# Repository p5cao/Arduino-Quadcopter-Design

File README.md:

# Arduino-Quadcopter-Design
A creative class project to design the PCB board for a quadcopter as well as programming the firmware and implementing the PID controller for flight controls.
The picture of our quadcopter can be found on this gallery webpage.
https://photos.google.com/share/AF1QipN9F1jDYG9cubRXA-CwWNmIePdVq3RI0pVtxd35Kb-5K7d3aRKYkmTJEXwJQgeCqA/photo/AF1QipMYG6V8wfTyHqf-2jjKtqaBbs2ouibxToXAU-El?key=cHRpcUZwaGp2eWJNbW5EVUltc3VJQ0NNVlZvN3FB

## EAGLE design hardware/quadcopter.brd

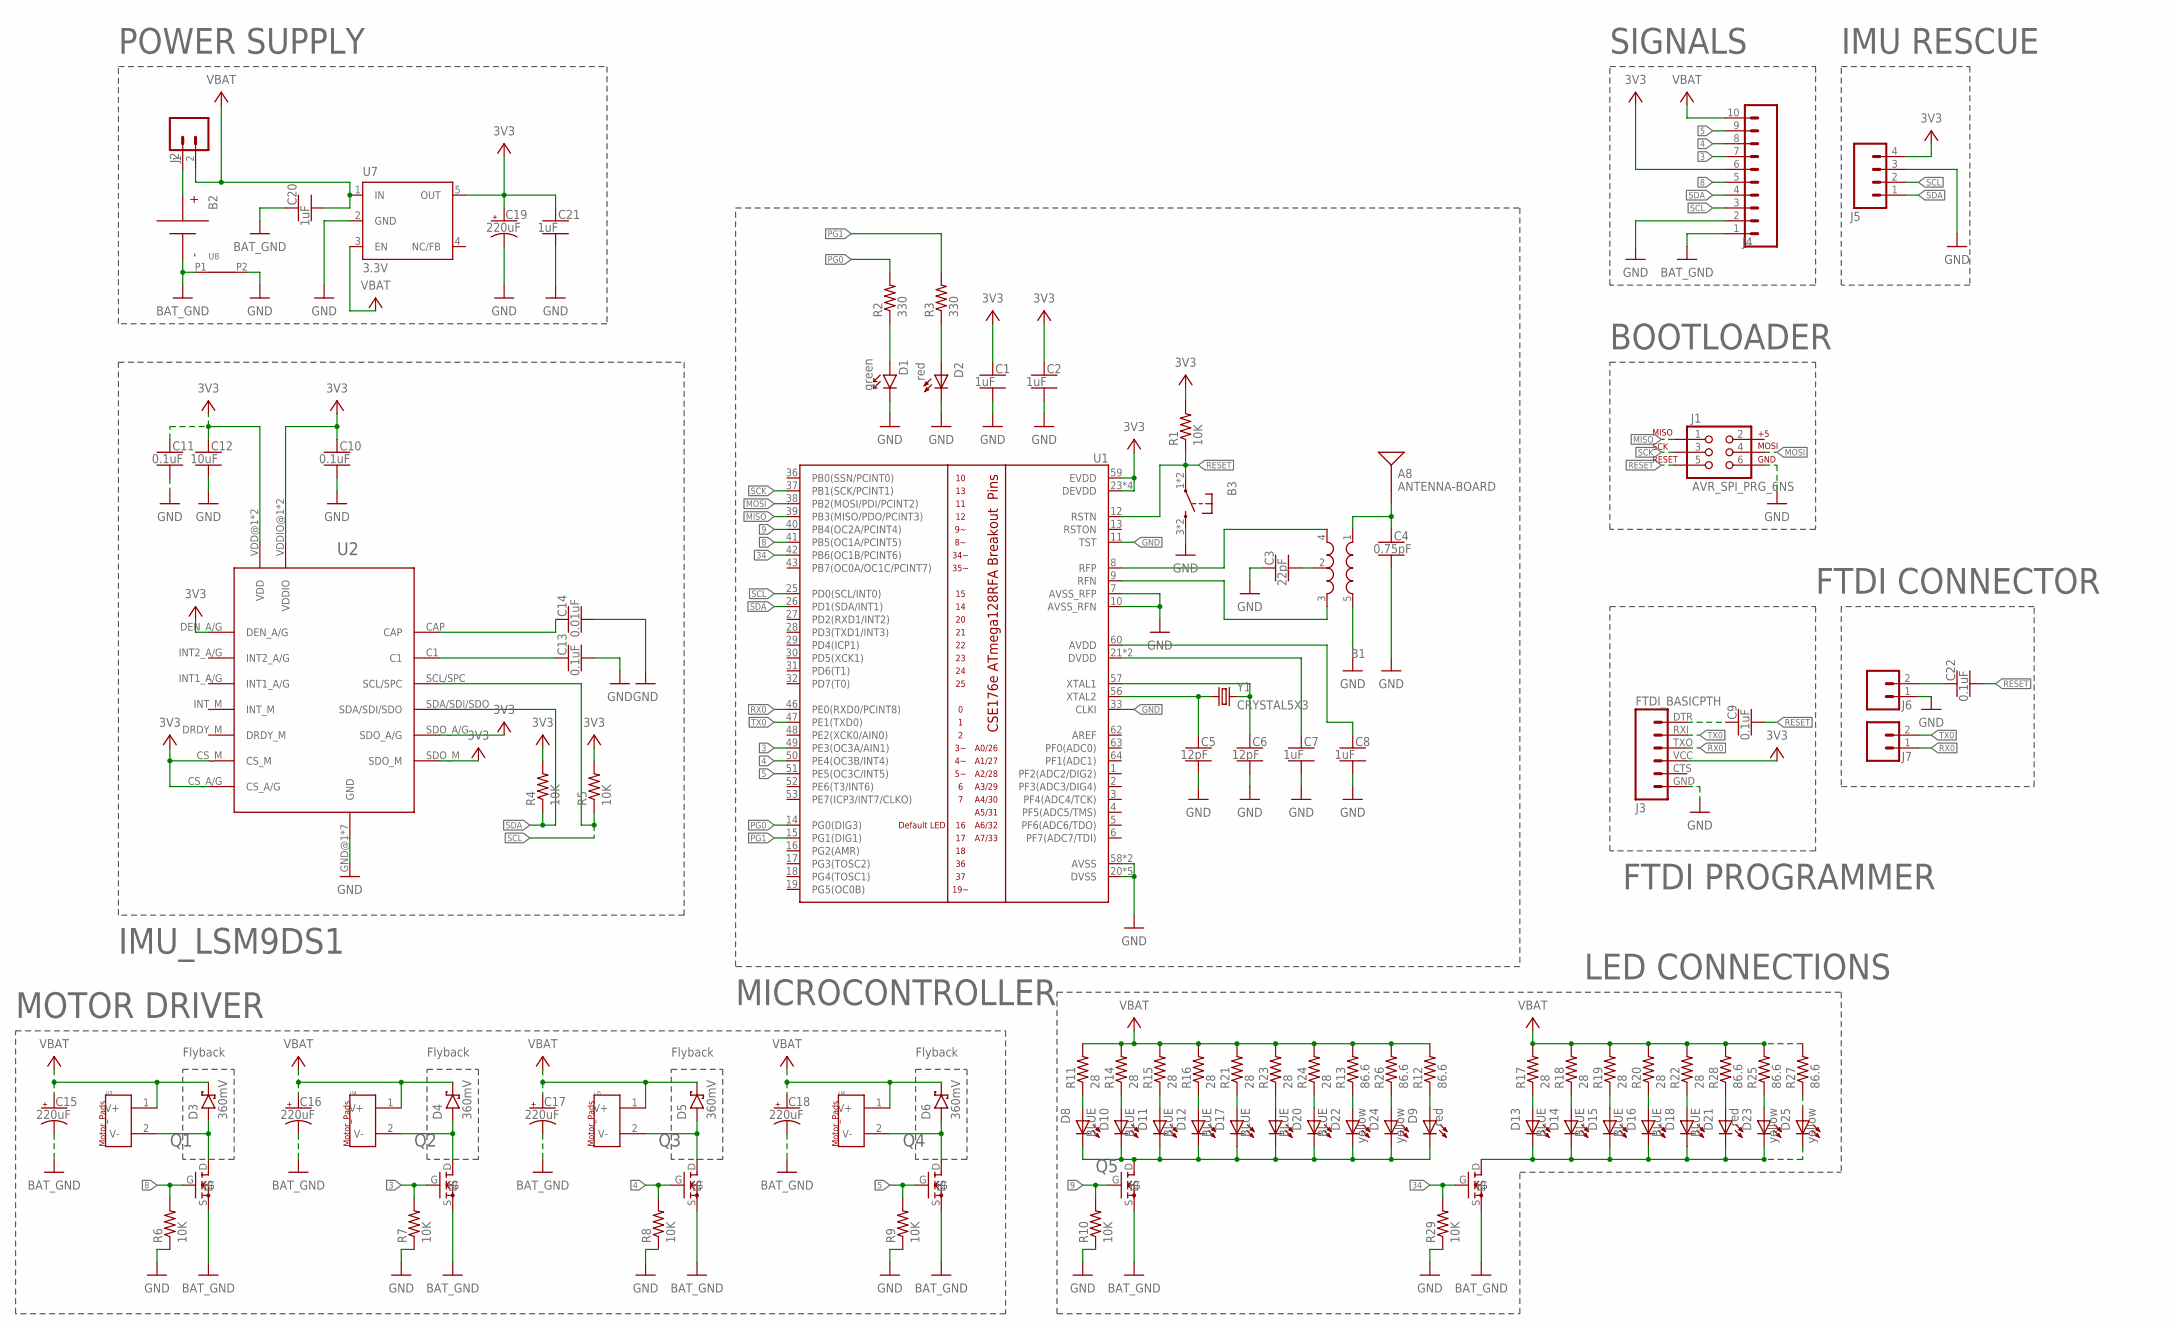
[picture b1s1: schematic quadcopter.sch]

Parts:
A8: ANTENNA-BOARD; ANT_PCB_2.4GHZ_NRF8001_1.6MM_1OZ
B1: BALUN0805; BALUN
B2: BATTERY-SCREW-TERMINAL; SCREW-TERMINAL-1X2-2.54MM
B3: PUSHBUTTON_-4.5X4.5; 4.5MM_TACTILE_SWITCH_TL3305AF160QG
C1, C2, C7, C8, C20, C21: 1uF; CAPC2012X140_HS
C3: 22pF; CAPC2012X140_HS
C4: 0.75pF; CAPC2012X140_HS
C5, C6: 12pF; CAPC2012X140_HS
C9, C10, C11, C13, C22: 0.1uF; CAPC2012X140_HS
C12: 10uF; CAPC2012X140_HS
C14: 0.01uF; CAPC2012X140_HS
C15, C16, C17, C18, C19: 220uF; CAPMP7343X310_HS
D1: green; LEDSC125X200X120-2_HS
D2: red; LED
D3, D4, D5, D6: 360mV; SOD3716X135_HS
D8, D10, D11, D12, D13, D14, D15, D16, D17, D18, D19, D20: BLUE; DIODE-LED-LTST-C170
D9, D21: red; DIODE-LED-LTST-C170
D22, D23, D24, D25: yellow; DIODE-LED-LTST-C170
J1: AVR_SPI_PRG_6NS; 2X3-NS
J2: HEADER-0.1IN-2POS-MALE; HDRV2W63P254_2X1_508X254H838_HS
J3: FTDI_BASICPTH; FTDI_BASIC
J4: HEADER-10POSTH-254X10; HDRV10W63P254_10X1_2540X254H838_HS
J5: HEADER-4POS-0.1IN-FEMALE; HDRVR4W80P254_1X4_1066X254X850B
J6, J7: HEADER-0.1IN-2POS-FEMALE; HDRV2W63P254_2X1_508X254H838_HS
Q1, Q2, Q3, Q4, Q5, Q6: MOSFET-VISHAY-SOT23-N-MOSFET; SOT-23_N_MOSFET
R1, R4, R5, R6, R7, R8, R9, R10, R29: 10K; RESC2012X60_HS
R2, R3: 330; RESC2012X60_HS
R11, R14, R15, R16, R17, R18, R19, R20, R21, R22, R23, R24: 28; RESC2012X60_HS
R12, R13, R25, R26, R27, R28: 86.6; RESC2012X60_HS
U1: ATMEGA128RFA1; QFN-64
U2: IMU_LSM-ST-LSM9DS1-IMU-LGA; LSM9DS1_IMU
U3, U4, U5, U6: MOTOR_PADS-MOLEX-0530470210; MOLEX-0530470210
U7: 3.3V; SOT23-DBV
U8: NET_BRIDGE-BRIDGE-SMD; NET_BRIDGE
Y1: CRYSTAL5X3; CRYSTAL-SMD-5X3

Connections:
3: J4.7, Q2.G, R7.2, U1.49 (PE3(OC3A/AIN1))
3V3: C1.1, C2.1, C10.1, C11.1, C12.1, C19.1 (+), C21.1, J3.VCC (4), J4.6, J5.4, R1.2, R4.2, R5.2, U1.23 (DEVDD), U1.34 (DEVDD), U1.44 (DEVDD), U1.54 (DEVDD), U1.59 (EVDD), U2.CS_A/G, U2.CS_M, U2.DEN_A/G, U2.SDO_A/G, U2.SDO_M, U2.VDD@1 (VDD), U2.VDD@2 (VDD), U2.VDDIO@1 (VDDIO), U2.VDDIO@2 (VDDIO), U7.5 (OUT)
4: J4.8, Q3.G, R8.2, U1.50 (PE4(OC3B/INT4))
5: J4.9, Q4.G, R9.2, U1.51 (PE5(OC3C/INT5))
8: J4.5, Q1.G, R6.2, U1.41 (PB5(OC1A/PCINT5))
9: Q5.G, R10.2, U1.40 (PB4(OC2A/PCINT4))
34: Q6.G, R29.2, U1.42 (PB6(OC1B/PCINT6))
BAT_GND: B2.1 (N), C15.2 (-), C16.2 (-), C17.2 (-), C18.2 (-), C20.1, J4.1, Q1.S, Q2.S, Q3.S, Q4.S, Q5.S, Q6.S, U8.P1
GND: B1.5 (GND), B3.3 (2), B3.4 (2), C1.2, C2.2, C3.1, C4.2, C5.2, C6.2, C7.2, C8.2, C10.2, C11.2, C12.2, C13.2, C14.2, C19.2 (-), C21.2, D1.C, D2.C, J1.6, J3.GND (6), J4.2, J5.3, J6.1, R6.1, R7.1, R8.1, R9.1, R10.1, R29.1, U1.7 (AVSS_RFP), U1.10 (AVSS_RFN), U1.11 (TST), U1.20 (DVSS), U1.24 (DVSS), U1.33 (CLKI), U1.35 (DVSS), U1.45 (DVSS), U1.55 (DVSS), U1.58 (AVSS), U1.61 (AVSS), U2.GND@1 (GND), U2.GND@2 (GND), U2.RES@1 (GND), U2.RES@2 (GND), U2.RES@3 (GND), U2.RES@4 (GND), U2.RES@5 (GND), U7.2 (GND), U8.P2
MISO: J1.1, U1.39 (PB3(MISO/PDO/PCINT3))
MOSI: J1.4, U1.38 (PB2(MOSI/PDI/PCINT2))
unnamed: A8.FEED, B1.1 (IN), C4.1
unnamed: B1.2 (GND), C3.2
unnamed: B1.4 (OUT1), U1.8 (RFP)
unnamed: B1.3 (OUT2), U1.9 (RFN)
unnamed: C5.1, U1.56 (XTAL2), Y1.1
unnamed: C6.1, U1.57 (XTAL1), Y1.3 (2)
unnamed: C7.1, U1.21 (DVDD), U1.22 (DVDD)
unnamed: C8.1, U1.60 (AVDD)
unnamed: D1.A, R2.1
unnamed: D2.A, R3.1
unnamed: C9.1, J3.DTR (1)
unnamed: C13.1, U2.C1
unnamed: C14.1, U2.CAP
unnamed: D3.A, Q1.D, U3.2 (V-)
unnamed: B2.2, J2.1
unnamed: D4.A, Q2.D, U4.2 (V-)
unnamed: D21.A, R28.1
unnamed: D5.A, Q3.D, U5.2 (V-)
unnamed: C22.1, J6.2
unnamed: D6.A, Q4.D, U6.2 (V-)
unnamed: D9.A, R12.1
unnamed: D24.A, R26.1
unnamed: D23.A, R25.1
unnamed: D22.A, R13.1
unnamed: D20.A, R24.1
unnamed: D19.A, R23.1
unnamed: D18.A, R22.1
unnamed: D17.A, R21.1
unnamed: D16.A, R20.1
unnamed: D15.A, R19.1
unnamed: D14.A, R18.1
unnamed: D13.A, R17.1
unnamed: D12.A, R16.1
unnamed: D11.A, R15.1
unnamed: D10.A, R14.1
unnamed: D8.A, R11.1
unnamed: D8.C, D9.C, D10.C, D11.C, D12.C, D17.C, D19.C, D20.C, D22.C, D24.C, Q5.D
unnamed: D13.C, D14.C, D15.C, D16.C, D18.C, D21.C, D23.C, D25.C, Q6.D
unnamed: D25.A, R27.1
PG0: R2.2, U1.14 (PG0(DIG3))
PG1: R3.2, U1.15 (PG1(DIG1))
RESET: B3.1, B3.2 (1), C9.2, C22.2, J1.5, R1.1, U1.12 (RSTN)
RX0: J3.TXO (3), J7.1, U1.46 (PE0(RXD0/PCINT8))
SCK: J1.3, U1.37 (PB1(SCK/PCINT1))
SCL: J4.3, J5.2, R5.1, U1.25 (PD0(SCL/INT0)), U2.SCL/SPC
SDA: J4.4, J5.1, R4.1, U1.26 (PD1(SDA/INT1)), U2.SDA/SDI/SDO
TX0: J3.RXI (2), J7.2, U1.47 (PE1(TXD0))
VBAT: C15.1 (+), C16.1 (+), C17.1 (+), C18.1 (+), C20.2, D3.C, D4.C, D5.C, D6.C, J2.2, J4.10, R11.2, R12.2, R13.2, R14.2, R15.2, R16.2, R17.2, R18.2, R19.2, R20.2, R21.2, R22.2, R23.2, R24.2, R25.2, R26.2, R27.2, R28.2, U3.1 (V+), U4.1 (V+), U5.1 (V+), U6.1 (V+), U7.1 (IN), U7.3 (EN)

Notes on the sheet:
MICROCONTROLLER
BOOTLOADER
FTDI PROGRAMMER
IMU_LSM9DS1
Flyback
MOTOR DRIVER
POWER SUPPLY
SIGNALS
IMU RESCUE
LED CONNECTIONS
FTDI CONNECTOR

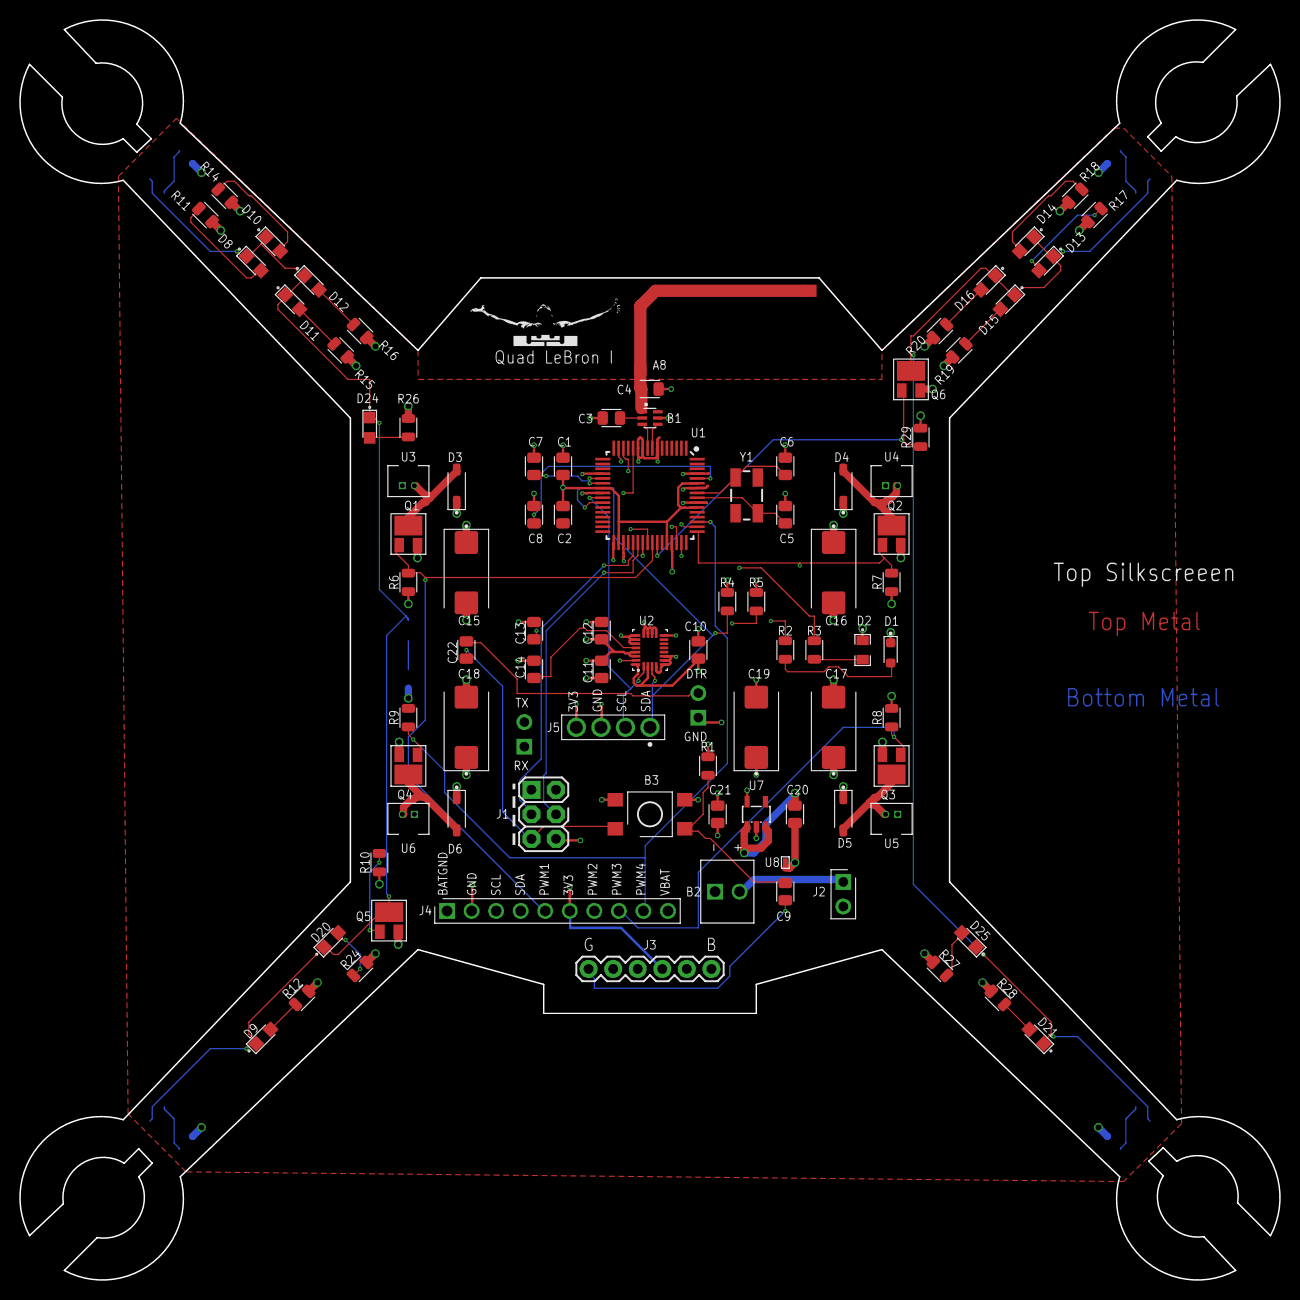
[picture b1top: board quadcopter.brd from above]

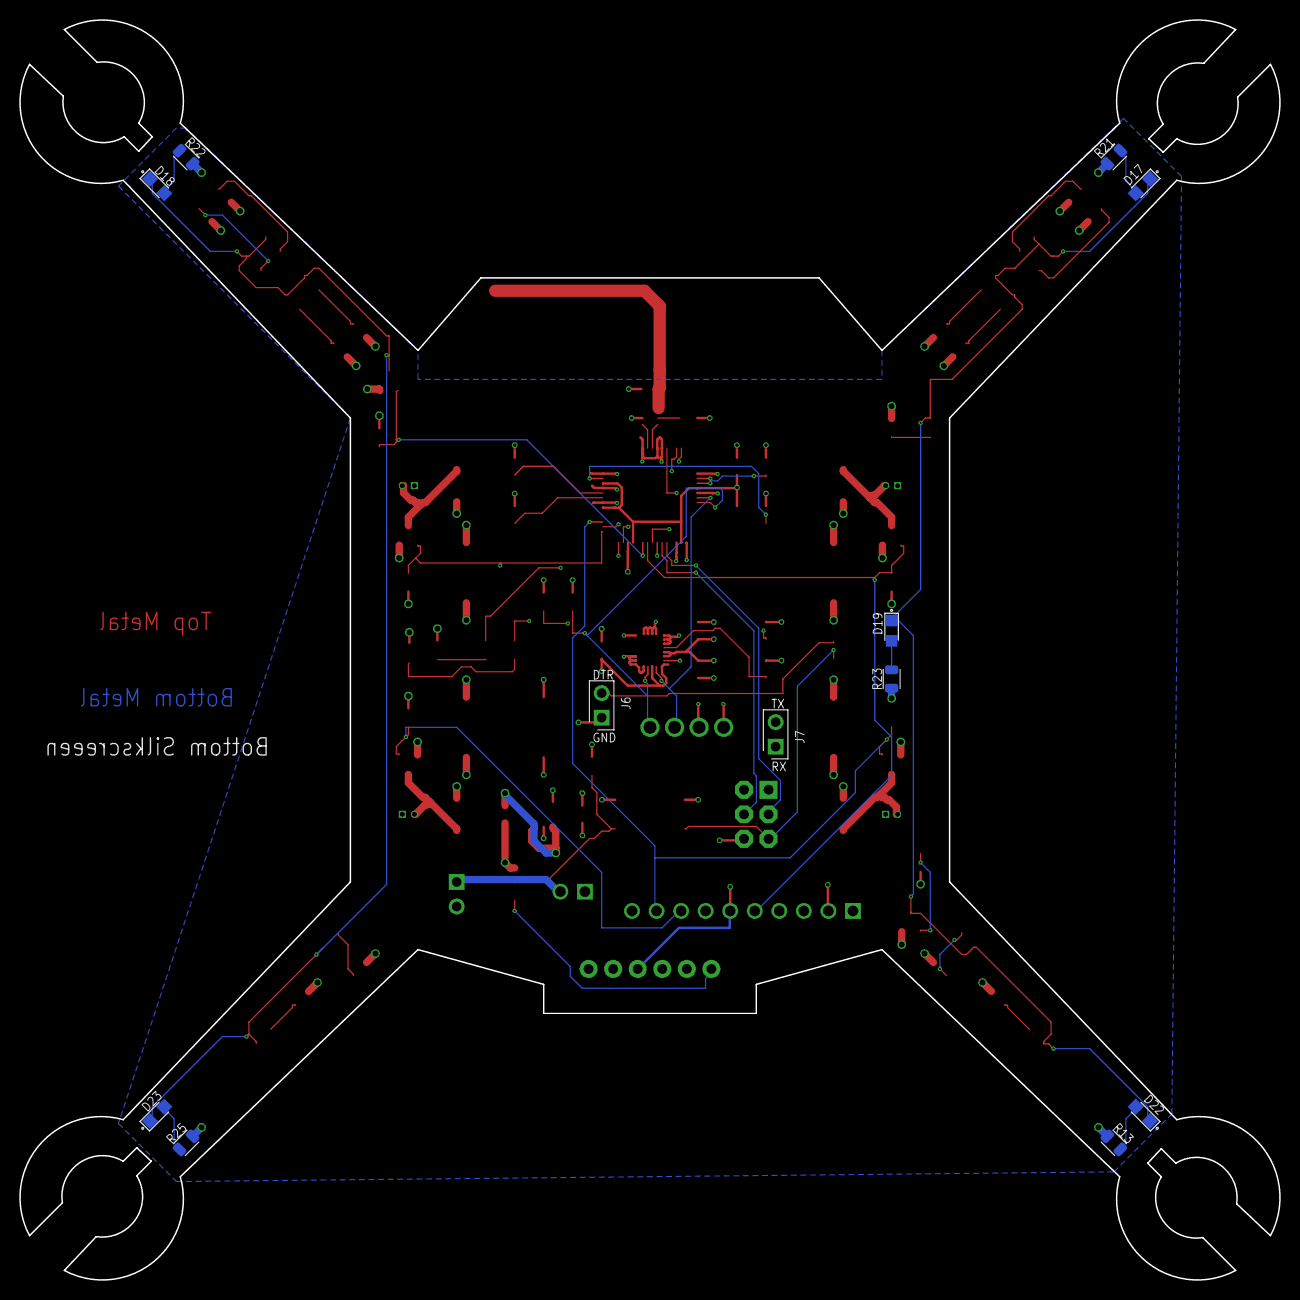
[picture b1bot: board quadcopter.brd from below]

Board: 4 copper layers, 130.4 x 130.4 mm, 103 parts (12 on the bottom side), 59 nets.

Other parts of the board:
U$1: LEBRON_JAMES
U$2: LAYER_LABELS

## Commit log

2019-04-09 Initial import
2019-04-09 add missing libraries
2019-04-09 remote software serial 2
2019-04-09 add the hacked up software serial librray to talk to lcd
2019-04-09 add software serial back
2019-04-25 board
2019-05-01 Create questions_about_their_board
2019-05-01 Rename questions_about_their_board to questions_about_their_board.txt
